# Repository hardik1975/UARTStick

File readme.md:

<!--  -->

<be>

# UART Stick 

<!-- ## 📌 Table of Contents

- [Overview](#-overview)
- [Features](#-features)
- [Specifications](#-specifications)
- [Getting Started](#-getting-started)
- [Use Cases](#-use-cases)
- [Installation](#-installation)
- [Repository Structure](#-repository-structure)
- [License](#-license)
- [Buy or Build](#-buy-or-build)
- [Contributing](#-contributing)
- [Contact](#-contact) -->

## Overview

Say hello to UART Stick — a micro-sized, Arduino-compatible USB to UART converter designed for makers, tinkerers, and embedded developers.

Unlike bulky boards, UART Stick is tiny, hassle-free, and packed with all the essential features you need to program your microcontrollers or read serial data — all while fitting directly into your USB port.

<!--  -->

## 🛒 Get Yours 

Fill out the [**Order Form**](https://docs.google.com/forms/d/e/1FAIpQLScuvlHv1w9dNxcGCHg3nWeYM4Ih8bzRdD5PpWKtMh8NcgmPcg/viewform?usp=header) to grab your UART Stick today!

<!-- Choose from two versions via our [**Order Form**](#): -->

Choose from two versions:

1. **DIY Kit** – Includes a bare PCB, CH340G IC, resistor, capacitor, ESD diode, and USB connector.  
  A great choice for learning and hands-on soldering practice!

2. **Fully Assembled** – Ready to use out of the box. Just plug it into your USB port and start programming!

Perfect for makers, students, and embedded devs — just plug and start building!

## Features

1. Compact Design – As small as a USB plug, perfect for on-the-go prototyping.
2. No Wires Needed – Built-in USB edge connector for direct plug-and-play.
3. CH340G Based – Reliable and widely supported USB-to-Serial IC.
4.  Open Source – Always will be. Hack it, mod it, or build your own.
5. Arduino-Compatible – Program boards via Arduino IDE effortlessly.
6. On-Board LEDs – Power, RX, and TX LEDs for easier debugging and status indication. 

## Specifications 

| Parameter        | Value                     |
|------------------|---------------------------|
| IC               | CH340G                    |
| USB Connector    | Edge-mounted USB-A        |
| Operating Voltage| 5V                        |
| Logic Level      | 3.3V or 5V                |
| Board Size       | 52.25mm x 12mm            |

## Getting Started

### What You’ll Need

1. Arduino IDE (or any serial monitor)
2. UART Stick
3. USB port
4. Jumper Wires

### Steps to Use

1. **Connect to Your Target Device**  
   Wire the UART Stick to your microcontroller or module as follows:

   | UART Stick Pin | Target Device     |
   |----------------|-------------------|
   | VCC            | 3.3V or 5V        |
   | RX             | TX                |
   | TX             | RX                |
   | GND            | GND               |

2. **Plug in the UART Stick**  
   Insert it directly into your computer’s USB port — no cables needed thanks to the edge USB connector.  

3. **Select the Correct COM Port**  
   Select correct COM port in Arduino IDE or your preferred serial tool.

4. **Start Communicating**

    - Upload code to your microcontroller
    - Or monitor serial data
    - Or send/receive commands

## 🔧 Use Cases

Here’s how UART Stick fits into your daily prototyping and debugging workflow:

1. **Flashing Firmware**  
  Upload code to microcontrollers like Arduino, ESP32, STM32, or ATmega-based boards with ease.

2. **Debugging Sensors & Modules**  
  View real-time data or debug sensor output via Serial Monitor.

3. **Reading BLE Data**  
  Communicate with BLE modules like HM-10 or HC-05/06 to send and receive wireless serial data.

4. **General UART Communication**  
  Interface with any device that speaks UART — from GPS modules to embedded Linux boards (like Raspberry Pi’s UART GPIOs).

5. **Serial Console Access**  
  Open terminal access to headless boards or dev kits, especially useful for bootloaders, Linux boards, or ESPs in flashing mode.

6. **Part of Your Embedded Toolbox**  
  A reliable companion for DIY projects, robotics, IoT devices, and lab debugging tasks.

## Contact

Made with ❤️ by Hardik

Have questions, feedback, or cool project ideas using the UART Stick?  
We’d love to hear from you!

- 💼 [LinkedIn](https://www.linkedin.com/in/hardik-seth-8687b7201) 
- 📺 [YouTube](https://www.youtube.com/@DIYwithHardik) 
- 📸 [Instagram](https://www.instagram.com/diywithhardik/) 
- 📧 [Email](mailto:hardikseth1975@gmail.com)

## Join Our WhatsApp Group 💬

Are you a maker, tinkerer, or electronics enthusiast?

Join our WhatsApp group to connect with like-minded people, share projects, get support, and behind the scenes!

👉 [**Click here to join the Community**](https://chat.whatsapp.com/JCH8m2oZNCG9Hrr31iBuLr)

## 📚 References

- 📄 [KiCAD Download Link](https://www.kicad.org/download/)  
- 📄 [CH340G Datasheet](https://static.efetividade.net/img/ch340g-datasheet-34852.pdf)   
- 📦 [USB Edge Connector Library](https://github.com/vasya-zh/PCB-Edge-USB-connector-KiCad-library)

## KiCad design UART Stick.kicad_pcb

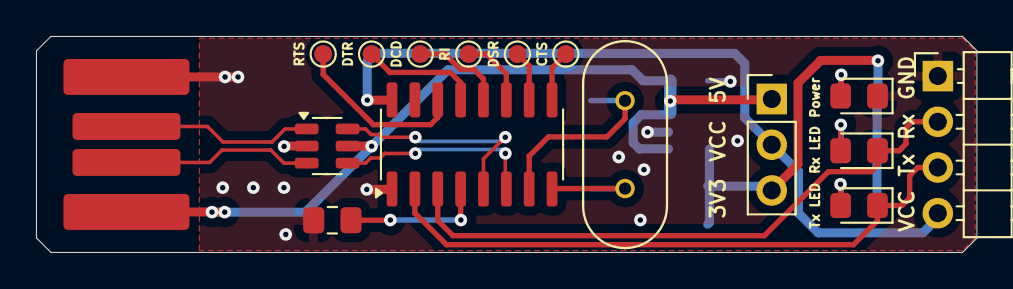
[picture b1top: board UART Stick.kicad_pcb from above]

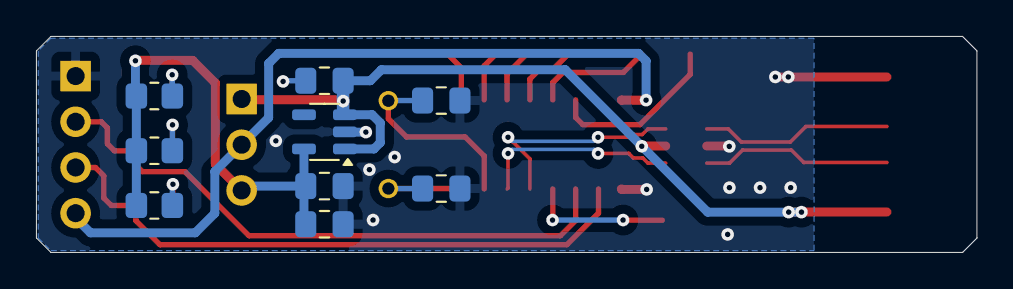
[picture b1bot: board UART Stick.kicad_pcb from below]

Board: 2 copper layers, 52.3 x 12.0 mm, 25 parts (9 on the bottom side), 22 nets.

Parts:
C1, C2: 22pF; C_0805_2012Metric_Pad1.18x1.45mm_HandSolder
C3: 10nF; C_0805_2012Metric_Pad1.18x1.45mm_HandSolder
C4, C6: 10uF; C_0805_2012Metric_Pad1.18x1.45mm_HandSolder
C5: 100nF; C_0805_2012Metric_Pad1.18x1.45mm_HandSolder
CTS: TestPoint; TestPoint_Pad_D1.0mm
D1: Tx_LED; LED_0805_2012Metric_Pad1.15x1.40mm_HandSolder
D2: Rx_LED; LED_0805_2012Metric_Pad1.15x1.40mm_HandSolder
D3: Power Led; LED_0805_2012Metric_Pad1.15x1.40mm_HandSolder
DCD: TestPoint; TestPoint_Pad_D1.0mm
DSR: TestPoint; TestPoint_Pad_D1.0mm
DTR: TestPoint; TestPoint_Pad_D1.0mm
J3: Conn_01x04_Pin; PinHeader_1x04_P2.54mm_Horizontal
J5: USB_A_PCB_Edge_receptacle
JP1: Jumper_3_Open; PinHeader_1x03_P2.54mm_Vertical
R1, R2, R3: 1k; R_0805_2012Metric_Pad1.20x1.40mm_HandSolder
RI: TestPoint; TestPoint_Pad_D1.0mm
RTS: TestPoint; TestPoint_Pad_D1.0mm
U1: CH340G; SOIC-16_3.9x9.9mm_P1.27mm
U2: USBLC6-2SC6; SOT-23-6
U3: SPX3819M5-L-3-3; SOT-23-5
Y2: HC-49_U-S16000000ABJB; XTAL_HC49P488W43L1150T466H350

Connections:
+3V3: C5.1, C6.1, JP1.3 (B), R1.1, R2.1, R3.1, U3.5 (OUT)
/USB_N: J5.2 (D-), U2.3 (I/O2)
/USB_P: J5.3 (D+), U2.1 (I/O1)
CH3_CTS: CTS.1, U1.9 (~CTS)
CH3_DCD: DCD.1, U1.12 (~DCD)
CH3_DSR: DSR.1, U1.10 (~DSR)
CH3_DTR: DTR.1, U1.13 (~DTR)
CH3_RI: RI.1, U1.11 (~RI)
CH3_RTS: RTS.1, U1.14 (~RTS)
CH3_Rx: D2.1 (K), J3.2, U1.3 (RXD)
CH3_Tx: D1.1 (K), J3.3, U1.2 (TXD)
GND: C1.2, C2.2, C3.2, C4.2, C5.2, C6.2, D3.1 (K), J3.1, J5.4 (GND), U1.1 (GND), U2.2 (GND), U3.2 (GND)
unnamed: D1.2 (A), R3.2
unnamed: D2.2 (A), R2.2
unnamed: D3.2 (A), R1.2
unnamed: C3.1, U1.4 (V3)
unnamed: C1.1, U1.7 (XI), Y2.1
unnamed: C2.1, U1.8 (XO), Y2.2
USB_D+: U1.5 (UD+), U2.6 (I/O1)
USB_D-: U1.6 (UD-), U2.4 (I/O2)
VBUS: C4.1, J5.1 (VBUS), JP1.1 (A), U2.5 (VBUS), U3.1 (IN), U3.3 (EN)
VCC: J3.4, JP1.2 (C), U1.16 (VCC)

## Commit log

2025-06-08 UART Stick - First commit
2025-06-08 Adding Readme file
2025-06-09 Adding WhatsApp Group Link
2025-06-09 Add UART Stick Image
2025-06-10 UART Stick image update
2025-06-10 Adding Google Form Link
